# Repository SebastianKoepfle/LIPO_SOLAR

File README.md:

LIPO_SOLAR
==========

Project LIPO charger for foldable solar modules
drawn in EAGLE 6.4.0

µC: PIC18F4520

with a LCD display for indication of charging performance, load status and output power
and a Voltmeter function up to 15V.

Intern LIPO 3000mAh 3,6V
On switch to load a external LIPO.

Output: USB(5V)

max Input Voltage 35V
max charging current 2A
max output current 2,5A

by FxSt

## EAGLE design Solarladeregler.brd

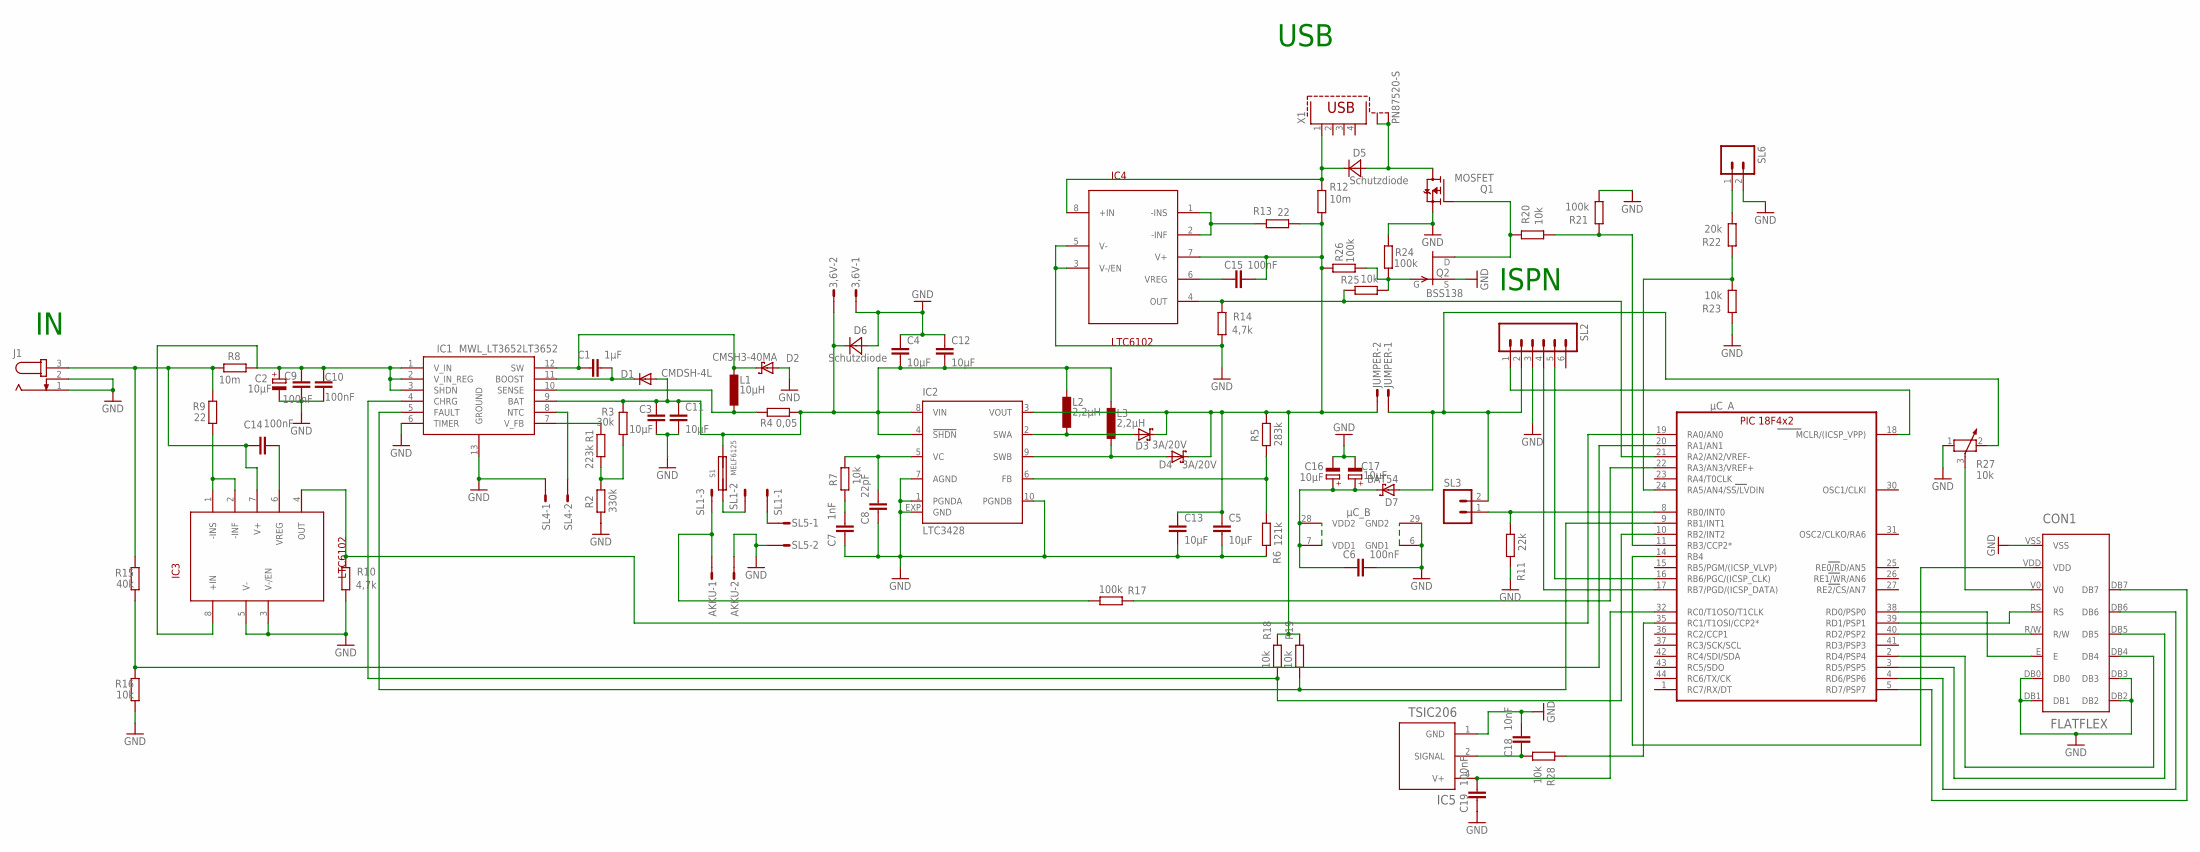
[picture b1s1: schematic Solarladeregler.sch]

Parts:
3,6V: M02S; 02P
AKKU: M02S; 02P
C1: 1µF; C0805
C2, C16, C17: 10µF; 153CLV-0505
C3, C4, C5, C11, C12, C13: 10µF; C0805
C6, C9, C10, C14, C15, C19: 100nF; C0805
C7: 1nF; C0805
C8: 22pF; C0805
C18: 10nF; C0805
CON1: FLATFLEX
D1: CMDSH-4L; SOD123
D2: CMSH3-40MA; SMB
D3, D4: 3A/20V; SMC
D5, D6: Schutzdiode; SMA
D7: BAT54; SOT23
IC1: MWL_LT3652LT3652; DFN12DD3X3
IC2: LTC3428; DFN10-3X3
IC3, IC4: LTC6102; MSOP8
IC5: TSIC206; SO08
J1: JACK-PLUG0; SPC4077
JUMPER: M02S; 02P
L1: 10µH; POWER-CHOKE_WE-TPC
L2, L3: 2,2µH; POWER-CHOKE_WE-TPC
Q1: MOSFET; TO252
Q2: BSS138; SOT23
R1: 223k; R0805
R2: 330k; R0805
R3: 30k; R0805
R4: 0,05; R0805
R5: 283k; R0805
R6: 121k; R0805
R7, R16, R18, R19, R20, R23, R25, R28: 10k; R0805
R8, R12: 10m; R2512
R9, R13: 22; R0805
R10, R14: 4,7k; R0805
R11: 22k; R0805
R15: 40k; R0805
R17, R21, R24, R26: 100k; R0805
R22: 20k; R0805
R27: 10k; PT-10
S1: MELF6125
SL1: M03S; 03P
SL2: M06; 06P
SL3, SL6: M02; 02P
SL4, SL5: M02S; 02P
X1: PN87520-S
µC: PIC18F4X2TQFP44; TQFP44

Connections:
GND: 3,6V.1, AKKU.2, C2.-, C3.2, C4.1, C5.2, C6.1, C7.2, C8.2, C9.2, C10.2, C11.2, C12.1, C13.2, C16.-, C17.-, C18.1, C19.2, CON1.DB0, CON1.DB1, CON1.DB2, CON1.DB3, CON1.VSS, D2.A, D6.A, IC1.6 (TIMER), IC1.13 (GROUND), IC2.1 (PGNDA), IC2.7 (AGND), IC2.10 (PGNDB), IC2.EXP (GND), IC3.3 (V-/EN), IC3.5 (V-), IC4.3 (V-/EN), IC4.5 (V-), IC5.1 (GND), J1.1, J1.2, Q1.2 (S), Q2.2 (S), R2.2, R6.2, R10.2, R11.2, R14.2, R16.2, R21.2, R23.1, R24.1, R27.1, SL2.3, SL4.1, SL5.2, SL6.2, µC.6 (GND1), µC.29 (GND2)
unnamed: CON1.E, µC.38 (RD0/PSP0)
unnamed: C1.1, D1.C, IC1.11 (BOOST)
unnamed: C2.+, C9.1, C10.1, IC1.1 (V_IN), IC1.2 (V_IN_REG), IC1.3 (SHDN), IC3.8 (+IN), R8.1
unnamed: IC1.10 (SENSE), L1.1, R4.2
unnamed: IC1.8 (NTC), SL4.2
unnamed: R1.2, R2.1, R3.1
unnamed: C1.2, D2.C, IC1.12 (SW), L1.2
unnamed: 3,6V.2, C3.1, C4.2, C11.1, C12.2, D1.A, D6.C, IC1.9 (BAT), IC2.4 (!SHDN), IC2.8 (VIN), L2.2, L3.2, R3.2, R4.1, S1.P$4
unnamed: C5.1, C13.1, C15.2, D3.C, D4.C, IC2.3 (VOUT), IC4.7 (V+), JUMPER.2, R5.1, R12.2, R13.2, R18.2, R19.2, R26.1
unnamed: D7.1 (A), JUMPER.1, R27.2, SL2.2, SL3.2
unnamed: D3.A, IC2.2 (SWA), L2.1
unnamed: C8.1, IC2.5 (VC), R7.1
unnamed: D4.A, IC2.9 (SWB), L3.1
unnamed: IC2.6 (FB), R5.2, R6.1
unnamed: C7.1, R7.2
unnamed: SL2.4, µC.17 (RB7/PGD/(ICSP_DATA))
unnamed: SL2.1, µC.18 (MCLR/(ICSP_VPP))
unnamed: SL2.5, µC.16 (RB6/PGC/(ICSP_CLK))
unnamed: IC3.1 (-INS), IC3.2 (-INF), R9.2
unnamed: C14.2, IC3.6 (VREG)
unnamed: IC3.4 (OUT), R10.1, µC.19 (RA0/AN0)
unnamed: D5.C, IC4.8 (+IN), R12.1, X1.1
unnamed: R11.1, SL3.1, µC.8 (RB0/INT0)
unnamed: IC4.1 (-INS), IC4.2 (-INF), R13.1
unnamed: C15.1, IC4.6 (VREG)
unnamed: IC4.4 (OUT), R14.1, R25.1, µC.21 (RA2/AN2/VREF-)
unnamed: R15.2, R16.1, µC.20 (RA1/AN1)
unnamed: IC1.7 (V_FB), R1.1
unnamed: R17.2, µC.22 (RA3/AN3/VREF+)
unnamed: AKKU.1, R17.1, SL1.3
unnamed: D5.A, Q1.3 (D), X1.S1, X1.S2
unnamed: SL1.1, SL5.1
unnamed: IC1.4 (CHRG), R18.1, µC.10 (RB2/INT2)
unnamed: IC1.5 (FAULT), R19.1, µC.9 (RB1/INT1)
unnamed: R20.2, R21.1, µC.11 (RB3/CCP2*)
unnamed: Q1.1 (G), Q2.1 (D), R20.1
unnamed: R22.2, SL6.1
unnamed: S1.P$3, SL1.2
unnamed: R22.1, R23.2, µC.24 (RA5/AN4/SS/LVDIN)
unnamed: Q2.3 (G), R24.2, R25.2, R26.2
unnamed: C6.2, C16.+, C17.+, D7.3 (C), µC.7 (VDD1), µC.28 (VDD2)
unnamed: C14.1, IC3.7 (V+), J1.3, R8.2, R9.1, R15.1
unnamed: CON1.RS, µC.39 (RD1/PSP1)
unnamed: CON1.R/W, µC.40 (RD2/PSP2)
unnamed: CON1.DB4, µC.2 (RD4/PSP4)
unnamed: CON1.DB5, µC.3 (RD5/PSP5)
unnamed: CON1.DB6, µC.4 (RD6/PSP6)
unnamed: CON1.DB7, µC.5 (RD7/PSP7)
unnamed: CON1.V0, R27.3
unnamed: R28.1, µC.35 (RC1/T1OSI/CCP2*)
unnamed: CON1.VDD, µC.14 (RB4)
unnamed: C19.1, IC5.4 (V+), µC.32 (RC0/T1OSO/T1CLK)
unnamed: C18.2, IC5.2 (SIGNAL), R28.2
OSC1/CLKI: µC.30 (OSC1/CLKI)
OSC2/CLKO/RA6: µC.31 (OSC2/CLKO/RA6)

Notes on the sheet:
USB
ISPN

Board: 2 copper layers, 78 parts (0 on the bottom side), 54 nets, no tracks yet.

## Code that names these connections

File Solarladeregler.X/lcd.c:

#include <xc.h>
#include <delays.h>
#include "lcd.h"


#define _LCDPORTD

#ifdef _LCDPORTD
#define E		PORTDbits.RD0
#define T_E		TRISDbits.TRISD0
#define RS		PORTDbits.RD1
#define T_RS		TRISDbits.TRISD1
#define RW		PORTDbits.RD2
#define T_RW		TRISDbits.TRISD2

#define DATA_P  	PORTD
#define TRIS_DATA_P	TRISD
#endif

#ifdef _LCDPORTC
#define E		PORTCbits.RC0
#define T_E		TRISCbits.TRISC0
#define RS		PORTCbits.RC1
#define T_RS		TRISCbits.TRISC1
#define RW		PORTCbits.RC2
#define T_RW		TRISCbits.TRISC2

#define DATA_P  	PORTC
#define TRIS_DATA_P	TRISC
#endif



//*****************************************************************************
//*****************************************************************************
void Delay_ms(int ms)
{
	 // Cycles = (1ms * Fosc) / 4 = (1ms * 8MHz) / 4 = 2000
	while(ms--)
		Delay1KTCYx(2);

}

//*****************************************************************************
//*****************************************************************************
unsigned char DisplayRead(char reg)
{
	unsigned char wert;

	TRIS_DATA_P |= 0xf0;

	RW=1;
        RS=reg;

	wert=0;

	E=1;
	E=1;
	E=1;
	wert=DATA_P & 0xf0;
	E=0;
	E=0;

	E=1;
	E=1;
	E=1;
	wert |= (DATA_P >> 4) & 0x0f;
	E=0;
	E=0;

	return wert;
}

//*****************************************************************************
//*****************************************************************************
void DisplayWrite(char reg, unsigned char d)
{
	TRIS_DATA_P &= 0x0f;
	DATA_P &= 0x0f;

	RW=0;
        RS=reg;

	E=1;
	E=1;
	DATA_P |= d & 0xf0;
	E=1;
	E=0;

	DATA_P &= 0x0f;
	Delay1TCY();

	E=1;
	E=1;
	DATA_P |= (d << 4) & 0xf0;
	E=1;
	E=0;

	Delay100TCYx(200);
}

//*****************************************************************************
//*****************************************************************************
void busy_lcd(void)
{
	unsigned char busy;

	do
	{
		busy=DisplayRead(0) & 0x80;
	} while(busy);
}

//*****************************************************************************
//*****************************************************************************
void LCD_Init(void)
{
	Delay_ms(15);

	DATA_P&= 0x0F;
	TRIS_DATA_P |= 0xf8; // Portbit 3 auf Eingang, da nicht benützt

	T_RW=0;
	T_RS=0;
	T_E=0;

	RW=0;
	RS=0;
	E=0;

	DisplayWrite(0,0x30);
	Delay_ms(5);

	DisplayWrite(0,0x30);
	Delay_ms(1);

	DisplayWrite(0,0x30);
	Delay_ms(1);

	DisplayWrite(0,0x20);
	Delay_ms(1);

	//Functionset, 4-Bit-Modus, 5*7 Punkte
	//Delay_ms(1);
	DisplayWrite(0,0x28);
	busy_lcd();

	// Display on/off
	DisplayWrite(0,0x0c);
	busy_lcd();

	// Display clear
	DisplayWrite(0,0x1);
	busy_lcd();

	// Set entry mode
	DisplayWrite(0,0x6);
	busy_lcd();
}

//*****************************************************************************
// links oben: x=1, y=1
//*****************************************************************************
void LCD_gotoxy(unsigned char x, unsigned char y)
{
	unsigned char adresse;

	switch(y)
	{
		case 1:
			adresse=0x00;
			break;
		case 2:
			adresse=0x40;
			break;
		case 3:
			adresse=0x14;
			break;
		case 4:
			adresse=0x54;
			break;
	}

	adresse += x-1;
	adresse |= 0x80;
	busy_lcd();
	DisplayWrite(0,adresse);
}

//*****************************************************************************
//*****************************************************************************
void LCD_string(char *text)
{
	while (*text != '\0')
	{
 		DisplayWrite(1,*text);
		text++;
	}
}

//*****************************************************************************
//*****************************************************************************
void LCD_string_xy(unsigned char x, unsigned char y,char *text)
{
	LCD_gotoxy(x,y);

	LCD_string(text);
}

//*****************************************************************************
//*****************************************************************************
void LCD_putc(unsigned char c)
{
	DisplayWrite(1,c);
	busy_lcd();
}

//*****************************************************************************
//*****************************************************************************
void LCD_Cursor_ON(void)
{
	DisplayWrite(0,0x0F);
}

//*****************************************************************************
//*****************************************************************************
void LCD_Cursor_OFF(void)
{
	DisplayWrite(0,0x0C);
}

//*****************************************************************************
//*****************************************************************************
void LCD_clear(void)
{
	DisplayWrite(0,0x01);
}

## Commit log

2013-12-29 Lipo Solar Projekt
2013-12-29 all files
2013-12-29 TSIC 206
    resistor +capacitor
2014-01-06 program
    program upload
